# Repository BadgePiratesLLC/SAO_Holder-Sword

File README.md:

# Badge Pirates 2022/23 Totem Project
2022 Totem Project

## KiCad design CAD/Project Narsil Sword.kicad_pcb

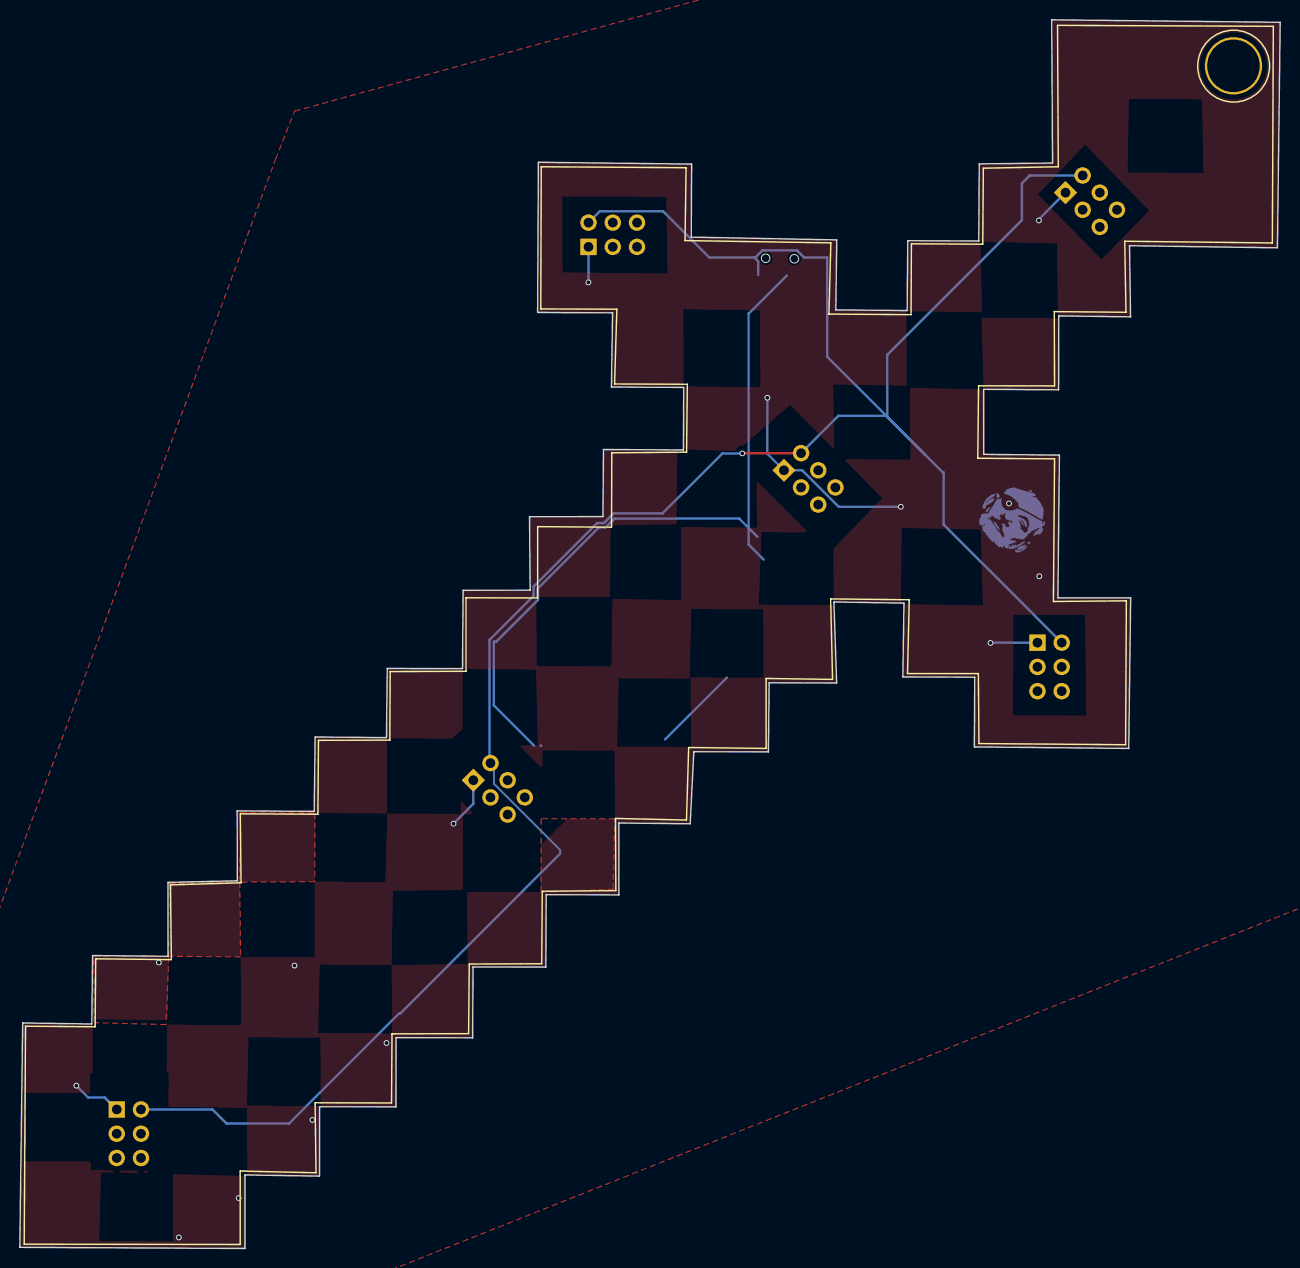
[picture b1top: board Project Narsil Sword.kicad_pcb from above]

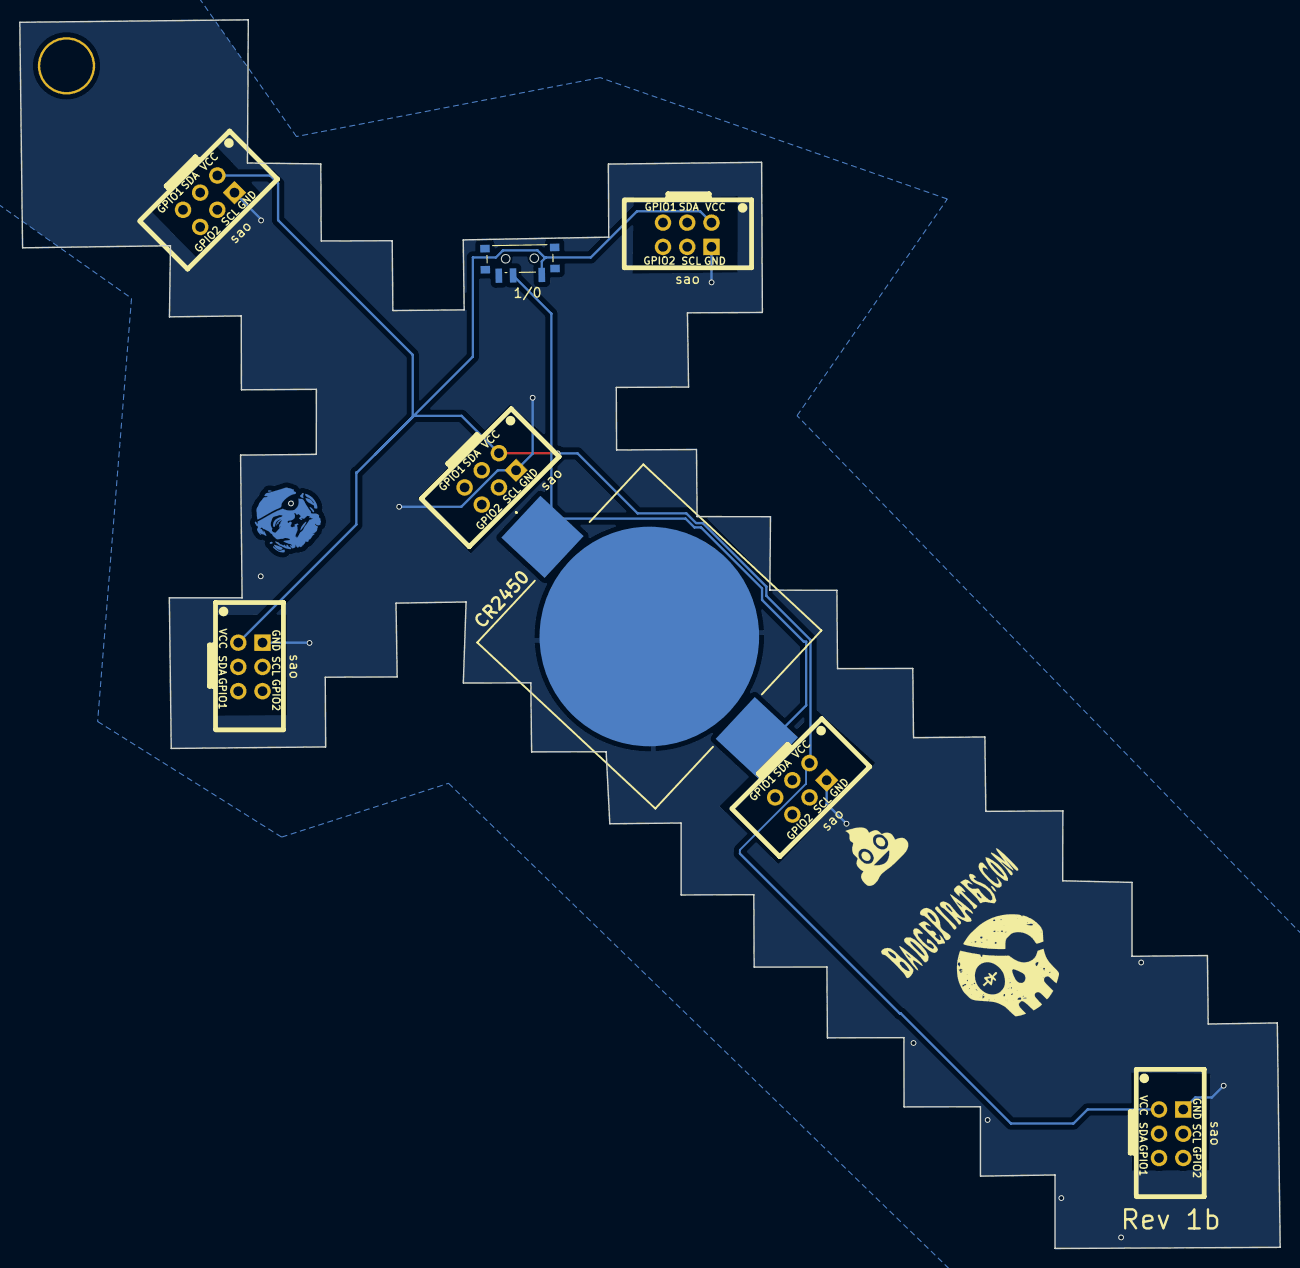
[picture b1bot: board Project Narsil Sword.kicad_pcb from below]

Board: 2 copper layers, 132.0 x 128.7 mm, 8 parts (2 on the bottom side), 3 nets.

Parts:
1/0: SW_SPDT; SW_SPDT_PCM12
U1: CR2450; BATHLD006SMT - CR2450
X1, X2, X3, X4, X5, X6: sao; Badgelife-SAOv169-SAO_Side_B.SLK

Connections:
+3V3: 1/0.2 (B), U1.1 (+_1)
GND: U1.2 (-), X1.2 (GND), X2.2 (GND), X3.2 (GND), X4.2 (GND), X5.2 (GND), X6.2 (GND)
VCC: 1/0.1 (A), X1.1 (VCC), X2.1 (VCC), X3.1 (VCC), X4.1 (VCC), X5.1 (VCC), X6.1 (VCC)

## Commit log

2022-06-06 Initial Commit
    Artwork and sample CAD
2022-06-11 update to files
2022-06-11 creating schematic
2022-06-13 Gerber Zips
2023-08-15 update Battery Footprint
2023-08-20 working on battery fix
2024-07-24 update with fixes, resize and Bigger battery
2024-08-17 pics
